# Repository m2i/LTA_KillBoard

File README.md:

LTA_KillBoard
=============

A dedicated power board for the Freshman 160 LTA's which provides power distribution and kill switch capabilities.

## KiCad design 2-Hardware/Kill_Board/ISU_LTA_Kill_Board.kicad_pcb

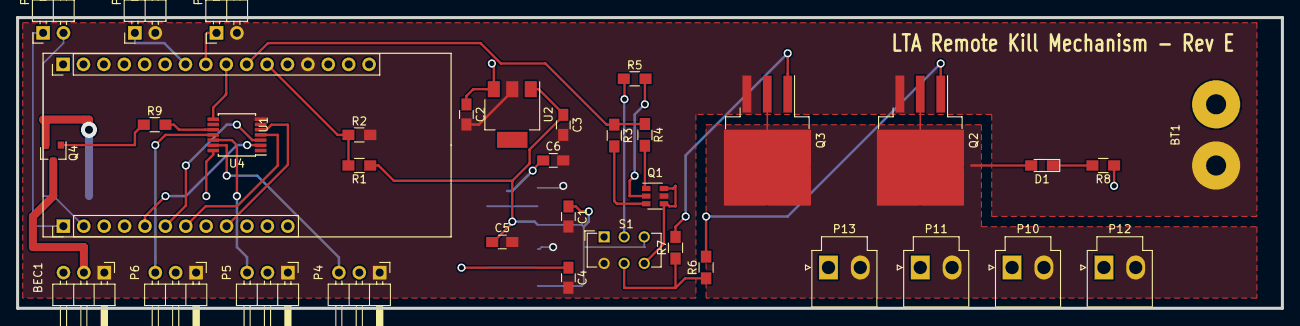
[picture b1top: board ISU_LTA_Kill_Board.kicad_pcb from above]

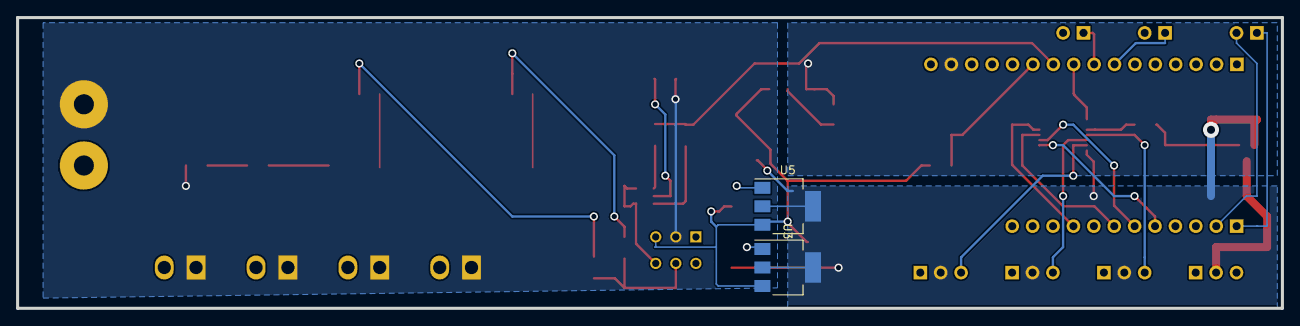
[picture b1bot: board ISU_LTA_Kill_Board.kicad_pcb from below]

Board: 2 copper layers, 157.5 x 36.2 mm, 38 parts (2 on the bottom side), 31 nets.

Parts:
BEC1: CONN_01X03; Pin_Header_Angled_1x03_Pitch2.54mm
BT1: BATTERY; SolderWirePad_2x_2-5mmDrill
C1, C3, C5: 0.1uF; C_0805_HandSoldering
C2, C4, C6: 10uF; C_0805_HandSoldering
D1: LED; LED_0805_HandSoldering
P1, P2, P3: CONN_01X02; Pin_Header_Angled_1x02_Pitch2.54mm
P4, P5, P6: CONN_01X03; Pin_Header_Angled_1x03_Pitch2.54mm
P10, P11, P12, P13: CONN_2; JST_VH_B2P-VH-B_2x3.96mm_Vertical
Q1: NMOS+PMOS; SOT-23-6
Q2, Q3: N-CH; TO-263-3_TabPin2
Q4: FDN359AN mfet; SOT-23
R1: 75K; R_0805_HandSoldering
R2: 33k; R_0805_HandSoldering
R3, R4, R5, R6, R7, R8: 330; R_0805_HandSoldering
R9: 2k; R_0805_HandSoldering
S1: DPDT; SW_CuK_JS202011CQN_DPDT_Straight
U1: ADAFRUIT_FEATHER; AdafruitFeather
U2: LM2937; SOT-223
U3, U5: AZ1117-5.0; SOT-223-3_TabPin2
U4: NTS0104; TSSOP-14_4.4x5mm_Pitch0.65mm

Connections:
+3.3V: C2.1, U1.15, U2.3
+5V: C4.1, C6.1, P4.2, P5.2, P6.2, Q4.2, U3.2, U4.14, U5.2
+BATT: BT1.1, P10.1, P11.1, P12.1, P13.1, R5.1, R8.1, S1.2
/Ctrl: R3.1, R4.1, U1.10
/High_Side: D1.2, P10.2, P11.2, P12.2, P13.2, Q2.2, Q3.2
/V_Sense: R1.2, R2.1, U1.11
GND: BEC1.1, BT1.2, C1.2, C2.2, C3.2, C4.2, C5.2, C6.2, P2.2, P3.2, P4.1, P5.1, P6.1, Q1.5, Q2.3, Q3.3, R2.2, S1.4, U1.13, U2.2, U3.1, U4.7, U5.1
unnamed: BEC1.2, Q4.3
unnamed: C1.1, C3.1, C5.1, R1.1, S1.3, U2.1, U3.3, U5.3
unnamed: D1.1, R8.2
unnamed: P1.1, U1.28
unnamed: P1.2, U1.27
unnamed: P2.1, U1.7
unnamed: P3.1, U1.8
unnamed: P4.3, U4.13
unnamed: P5.3, U4.12
unnamed: P6.3, U4.11
unnamed: Q1.1, R4.2
unnamed: Q1.2, R5.2
unnamed: Q1.3, R3.2
unnamed: Q1.4, Q1.6, S1.6
unnamed: Q2.1, R6.2
unnamed: Q3.1, R7.2
unnamed: Q4.1, R9.1
unnamed: R6.1, R7.1, S1.5
unnamed: R9.2, U4.10
unnamed: U1.9, U4.8
unnamed: U1.20, U4.5
unnamed: U1.22, U4.4
unnamed: U1.23, U4.3
unnamed: U1.24, U4.2

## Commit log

2013-10-10 Initial commit of the files.
2013-11-20 2013 for Rev D by Eli
2013-12-10 Updated the battery cutoffs and the battery voltage display values.
2016-07-11 Work on new Rev. E board
    Initial start on Rev. E Board.
2016-10-03 Initial SW for new hardware boards
2016-10-23 Added some prelim code
2016-10-23 Added Shield unit
    Added the 3D design of the shields.
2016-11-03 Start of moving to Feather board
2016-11-18 Update to schematic with new feather part
2016-11-24 minor update
2016-12-14 Update to Shield
2017-07-10 Circuit clean up
    Removed flip flop (not needed). Moved a connector off pin 9 since it
    is tied to monitor internal battery. Right now, board is powered from
    on board reg and not the feather reg. Disabled feather regulator
2017-07-10 Updates to modules
    Updated to mapping parts to modules
2017-07-14 Start of design for laser cannon
    not finished yet.
2017-07-19 update to cannon
2018-03-14 derp
2018-07-30 Updates to schematic
    added current sense resistor, added buzzer.
2018-10-30 Fixed some issues with the schedmatic
2018-10-31 Getting ready for fab
    Unable to make board. Footprint for Feather is lost, started working on new footprint but not complete yet.
2018-10-31 Got correct footprint for feather, placed all parts on board
2018-10-31 Update to board
2018-11-01 Adding pours
    Not done just moving to a new computer.
2018-11-01 Fixed pwm to have 3.3 v power and then added traces.
2018-11-01 Reduced through holes and fixed the ground issue on one mos
2018-11-04 Nothing big
2018-11-27 Update for bec add
    Added 5v regulator and tied pwm power to them
2019-02-20 Updated to have BEC and level shifter
2019-02-20 FIxing pad clearence
2019-02-22 IDK WHAT CHANGED......
2019-09-26 Fixed power distro
2019-09-27 Fixed some of the power plane issues. forgot to update them to solid for the power planes. gnd was already fixed.
2021-12-22 Added two new connectors
2022-01-12 Auto stash before merge of "Rev-E" and "origin/Rev-E"
2022-01-13 Minor update to address Vreg issues.
2022-12-14 New Revision
2022-12-14 Added IR stuff
